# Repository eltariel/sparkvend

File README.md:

# SparkVend
This is a collection of bits that allows a device to communicate with a vending machine that
implements the MDB/ICP standard.

## Ok, what?
At [SparkCC](https://sparkcc.org) we have a bunch of vending machines. Of these, at least one
talks MDB/ICP, which is a protocol that connects a VMC (vending machine controller) to a number
of devices, like coin mechs, bill acceptors, and cashless (credit card etc) devices. There's been
a long-standing project idea to actually *use* this vending machine, probably for common components
for projects, but managing money is a lot of effort and we could do it another way if we had the
interface.

So. I'm building one.

There's a lot of info floating around about how these things work, but I wanted to learn how to do
a heap of things, so I'm building it from scratch instead.

The biggest complication for this interface is the electronic interface - an opto-isolated
multidrop serial bus isn't a big deal on its own, but finding a UART that supports 9-bit
communications is a little less straightforward. A lot of microcontrollers have these, but then we
want to hook the vending machine to more powerful systems so we don't have to deal with low-level
considerations when we eventually build something way more complex than it needs to be.

Many of the design decisions for this project come from the contents of my gadget bin, as well as
my own abilities:
- MDB/ICP protocol implemented on a Teensy 3.x because I have spares
- Host system is (going to be) a Raspberry Pi because they're everywhere
- PCB design is mostly through-hole because I can just about manage to solder well enough for that

## Setup
This project has a bunch of filters defined to keep the KiCad files as git-friendly as possible. To
set this up correctly, run this:

    git config include.path ../extra.gitconfig

For more info about the filters, see [here](https://jnavila.github.io/plotkicadsch/).

## Repo Layout
### /
Contains project global stuff:
- This README
- Licensing info
- Additional git configuration

### /hardware
Schematics and PCB layouts for the board that connects all of the pieces together. Uses KiCad v5.

### /teensy
MDB/ICP interface firmware for the Teensy. This acts as MDB Cashless Device 1 (0x10). Uses
Teensyduino via PlatformIO, because the Arduino IDE is... weird.

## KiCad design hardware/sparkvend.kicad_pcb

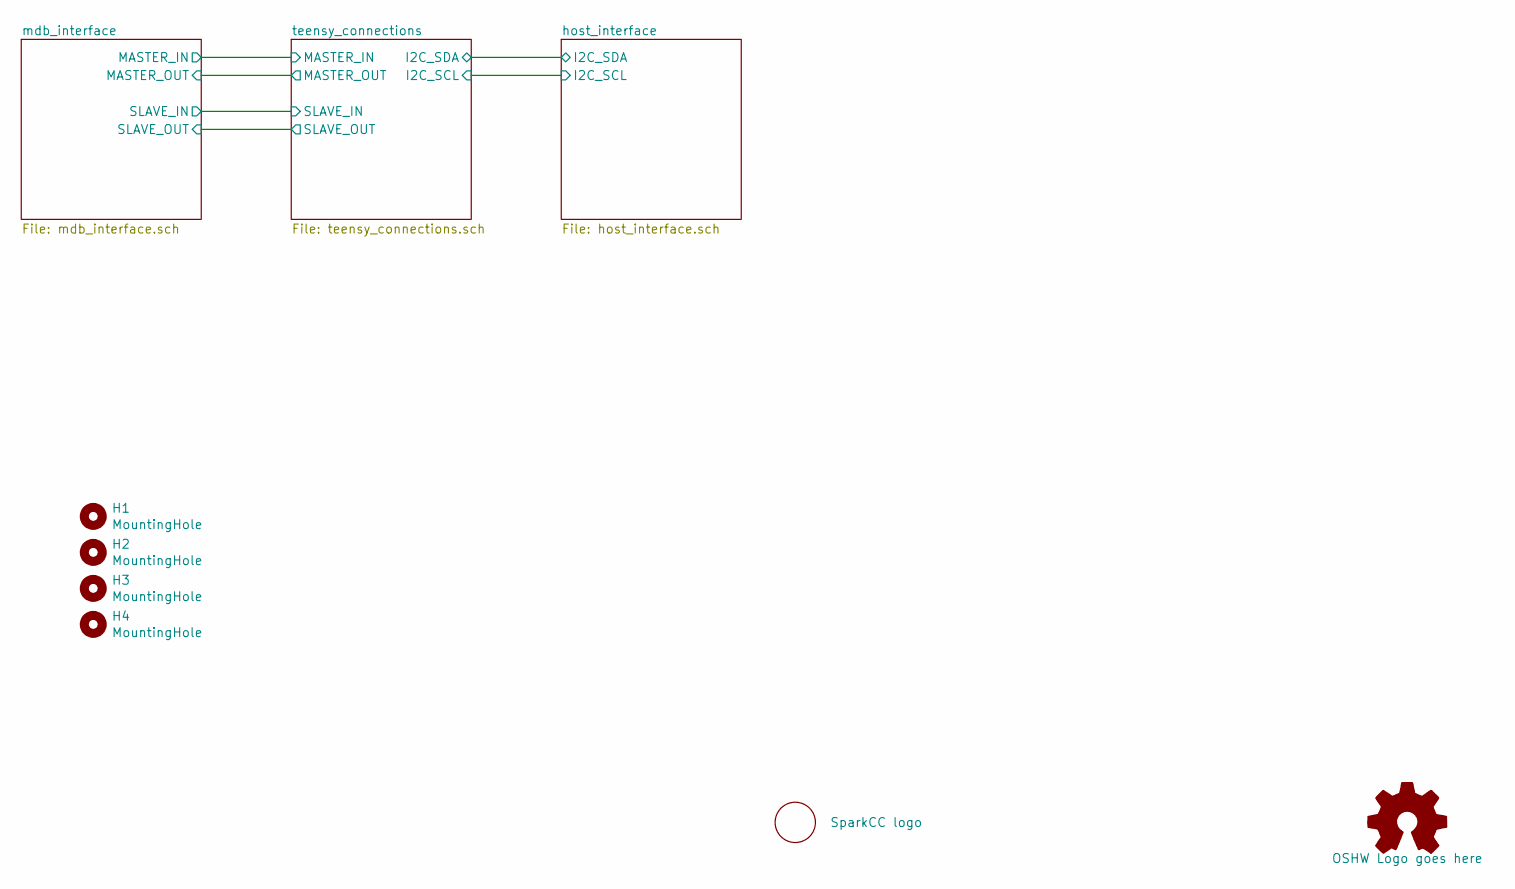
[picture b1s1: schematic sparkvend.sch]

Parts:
H1, H2, H3, H4: MountingHole; MountingHole_2.7mm_M2.5
LOGO1: SparkCC logo; SPARKCC_LOGO
LOGO3: OSHW Logo goes here; OSHW-Logo2_7.3x6mm_SilkScreen

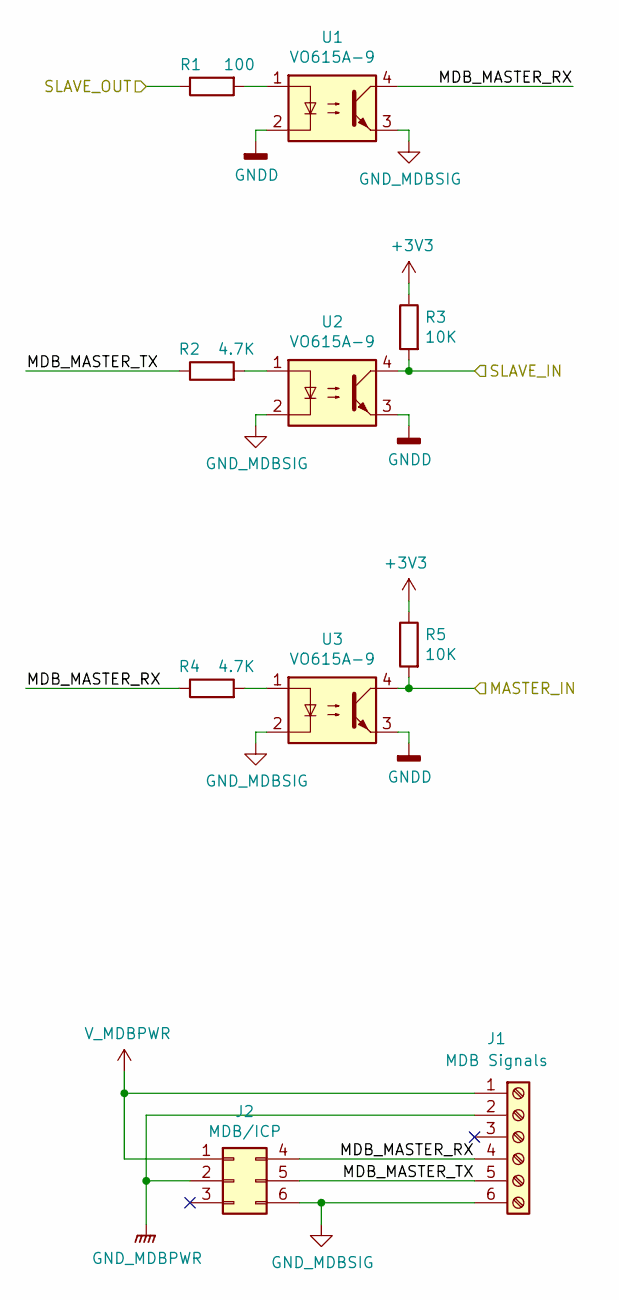
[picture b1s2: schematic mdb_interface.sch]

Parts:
J1: MDB Signals; SCREWTERMINAL-3.5MM-6
J2: MDB/ICP; Molex_Mini-Fit_Jr_5569-06A2_2x03_P4.20mm_Horizontal
R1: 100; R_Axial_DIN0207_L6.3mm_D2.5mm_P7.62mm_Horizontal
R2, R4: 4.7K; R_Axial_DIN0207_L6.3mm_D2.5mm_P7.62mm_Horizontal
R3, R5: 10K; R_Axial_DIN0207_L6.3mm_D2.5mm_P7.62mm_Horizontal
U1, U2, U3: VO615A-9; DIP-4_W7.62mm

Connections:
+3V3: R3.1, R5.1; also elsewhere on the board
/mdb_interface/MASTER_IN: R5.2, U3.4; also elsewhere on the board
/mdb_interface/MDB_MASTER_RX: J1.4, J2.4, R4.1, U1.4
/mdb_interface/MDB_MASTER_TX: J1.5, J2.5, R2.1
/mdb_interface/SLAVE_IN: R3.2, U2.4; also elsewhere on the board
/mdb_interface/SLAVE_OUT: R1.1; also elsewhere on the board
GNDD: U1.2, U2.3, U3.3; also elsewhere on the board
GNDMDB: J1.2, J2.2
GND_MDBSIG: J1.6, J2.6, U1.3, U2.2, U3.2
unnamed: R1.2, U1.1
unnamed: R2.2, U2.1
unnamed: R4.2, U3.1
V_MDBPWR: J1.1, J2.1

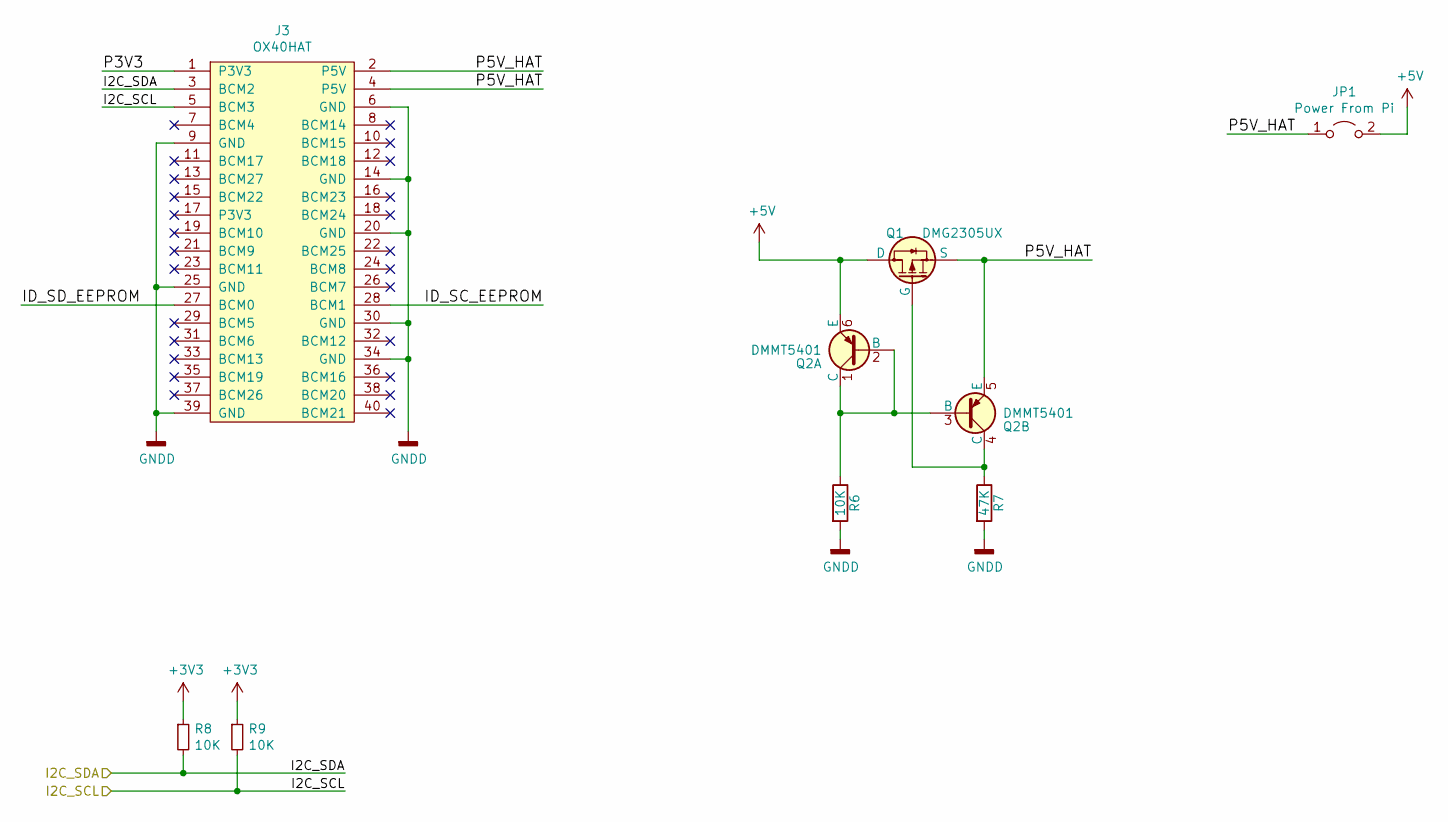
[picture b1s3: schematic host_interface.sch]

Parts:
J3: OX40HAT; PinSocket_2x20_P2.54mm_Vertical
JP1: Power From Pi; PinHeader_1x02_P2.54mm_Vertical
Q1: DMG2305UX; SOT-23
Q2: DMMT5401; SOT-23-6
R6: 10K; R_0603_1608Metric_Pad1.05x0.95mm_HandSolder
R7: 47K; R_0603_1608Metric_Pad1.05x0.95mm_HandSolder
R8, R9: 10K; R_Axial_DIN0207_L6.3mm_D2.5mm_P7.62mm_Horizontal

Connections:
+3V3: R8.1, R9.1; also elsewhere on the board
+5V: JP1.2 (B), Q1.3 (D), Q2.6 (E); also elsewhere on the board
/host_interface/I2C_SCL: J3.5 (BCM3), R9.2; also elsewhere on the board
/host_interface/I2C_SDA: J3.3 (BCM2), R8.2; also elsewhere on the board
/host_interface/ID_SC_EEPROM: J3.28 (BCM1)
/host_interface/ID_SD_EEPROM: J3.27 (BCM0)
/host_interface/P3V3: J3.1 (P3V3)
/host_interface/P5V_HAT: J3.2 (P5V), J3.4 (P5V), JP1.1 (A), Q1.2 (S), Q2.5 (E)
GNDD: J3.6 (GND), J3.9 (GND), J3.14 (GND), J3.20 (GND), J3.25 (GND), J3.30 (GND), J3.34 (GND), J3.39 (GND), R6.2, R7.2; also elsewhere on the board
unnamed: Q1.1 (G), Q2.4 (C), R7.1
unnamed: Q2.1 (C), Q2.2 (B), Q2.3 (B), R6.1

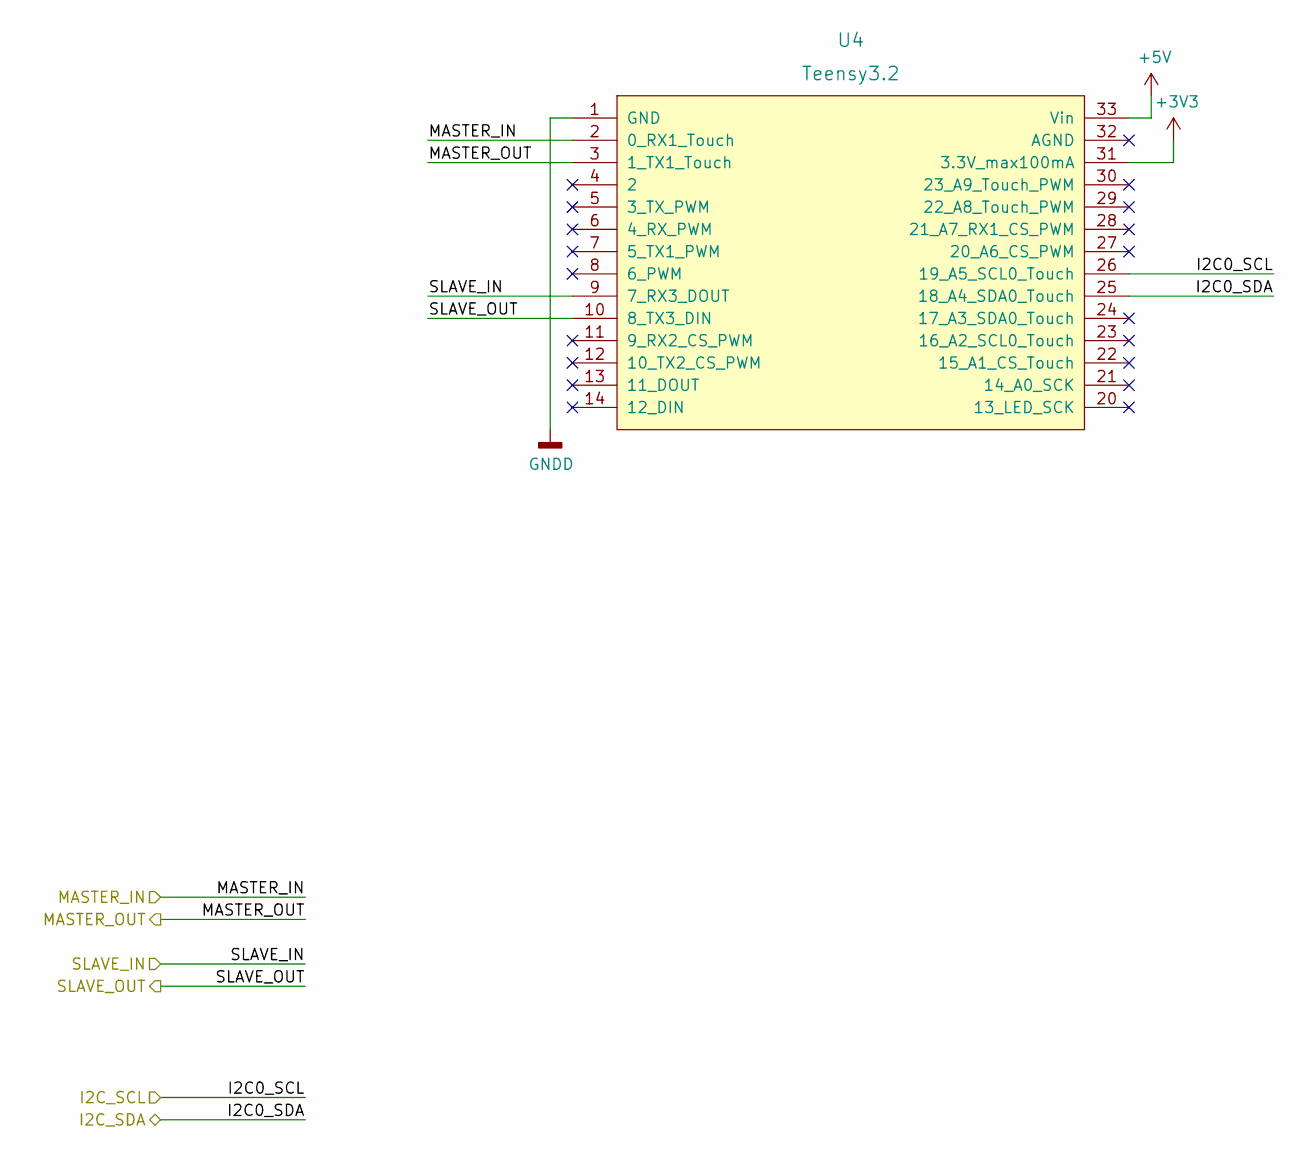
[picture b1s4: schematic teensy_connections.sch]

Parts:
U4: Teensy3.2; teensy-3.x-common

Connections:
+3V3: U4.31 (3.3V_max100mA); also elsewhere on the board
+5V: U4.33 (Vin); also elsewhere on the board
/host_interface/I2C_SCL: U4.26 (19_A5_SCL0_Touch); also elsewhere on the board
/host_interface/I2C_SDA: U4.25 (18_A4_SDA0_Touch); also elsewhere on the board
/mdb_interface/MASTER_IN: U4.2 (0_RX1_Touch); also elsewhere on the board
/mdb_interface/SLAVE_IN: U4.9 (7_RX3_DOUT); also elsewhere on the board
/mdb_interface/SLAVE_OUT: U4.10 (8_TX3_DIN); also elsewhere on the board
/teensy_connections/MASTER_OUT: U4.3 (1_TX1_Touch)
GNDD: U4.1 (GND); also elsewhere on the board

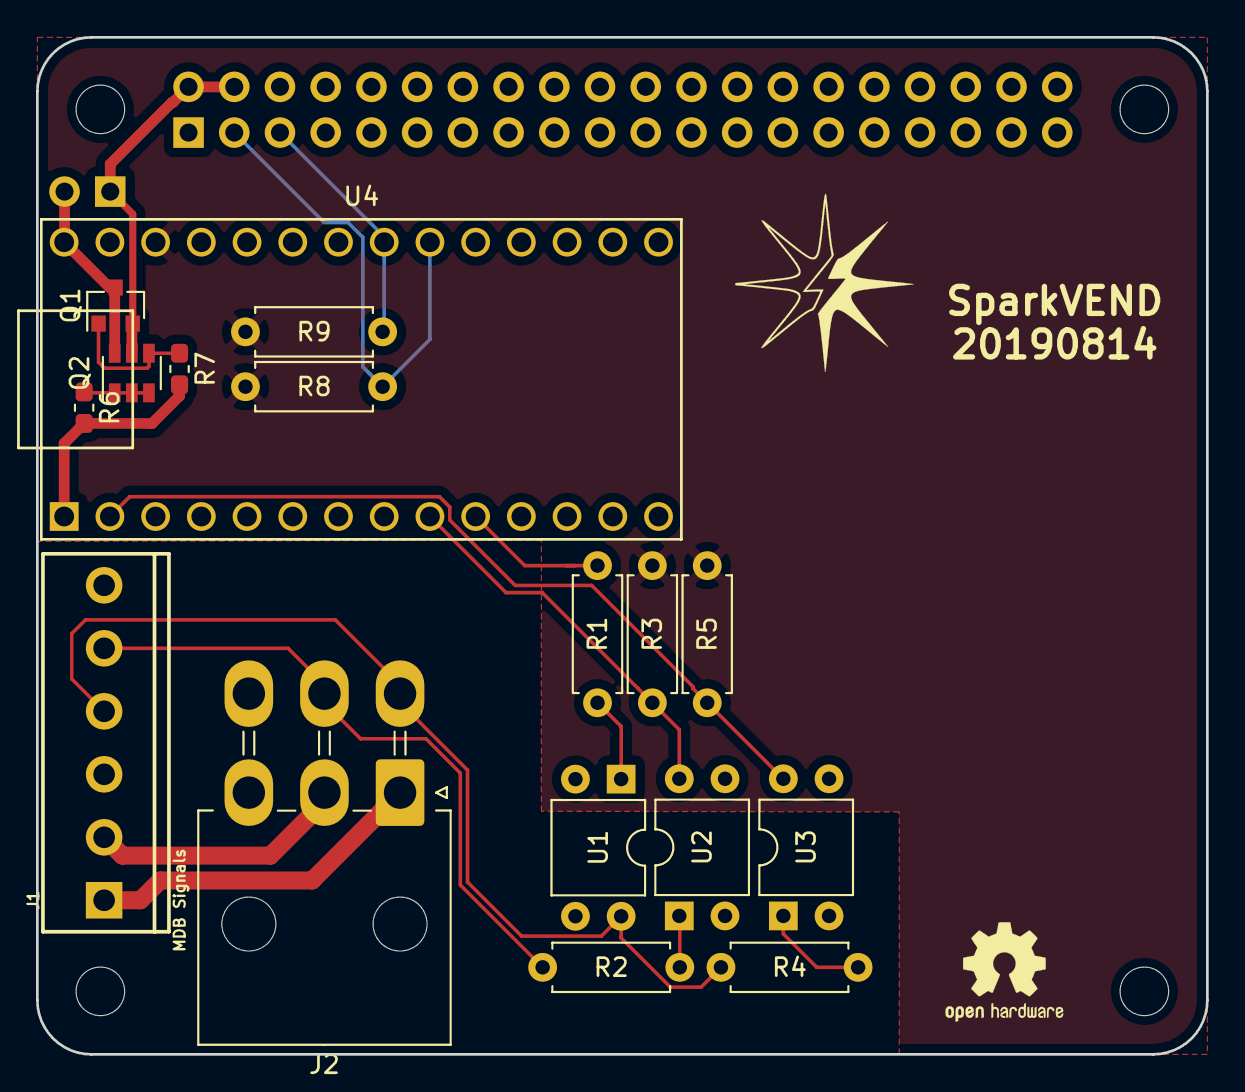
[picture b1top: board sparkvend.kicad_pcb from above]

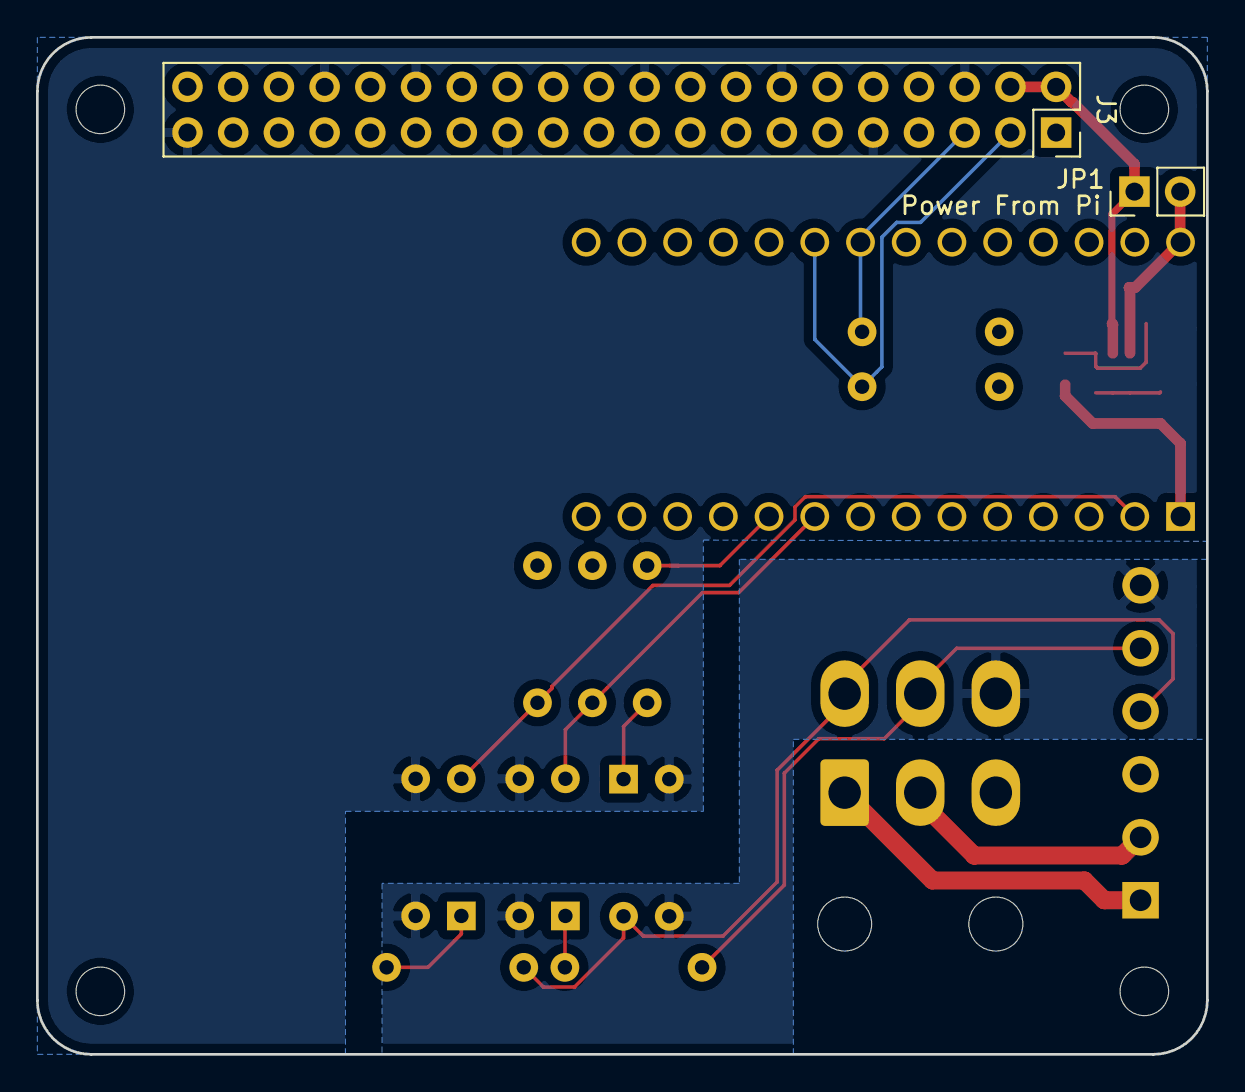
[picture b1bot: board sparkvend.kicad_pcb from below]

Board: 2 copper layers, 65.0 x 56.5 mm, 25 parts (2 on the bottom side), 19 nets.

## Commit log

2019-08-08 Here's a chunk of code.
2019-08-12 Changes after testing
2019-08-13 Added some more commands
2019-08-13 gitignore fix
2019-08-14 PCB, licensing
2019-08-14 Oops, forgot the README...
2019-08-14 Apparently I forgot how to do links in markdown
2019-08-17 Enough protocol to allow vending!
    - Cashless init works correctly
    - When in the Enabled state, every poll will start a vend session
    - Also, minor log changes
2019-08-23 Added I2C interface
